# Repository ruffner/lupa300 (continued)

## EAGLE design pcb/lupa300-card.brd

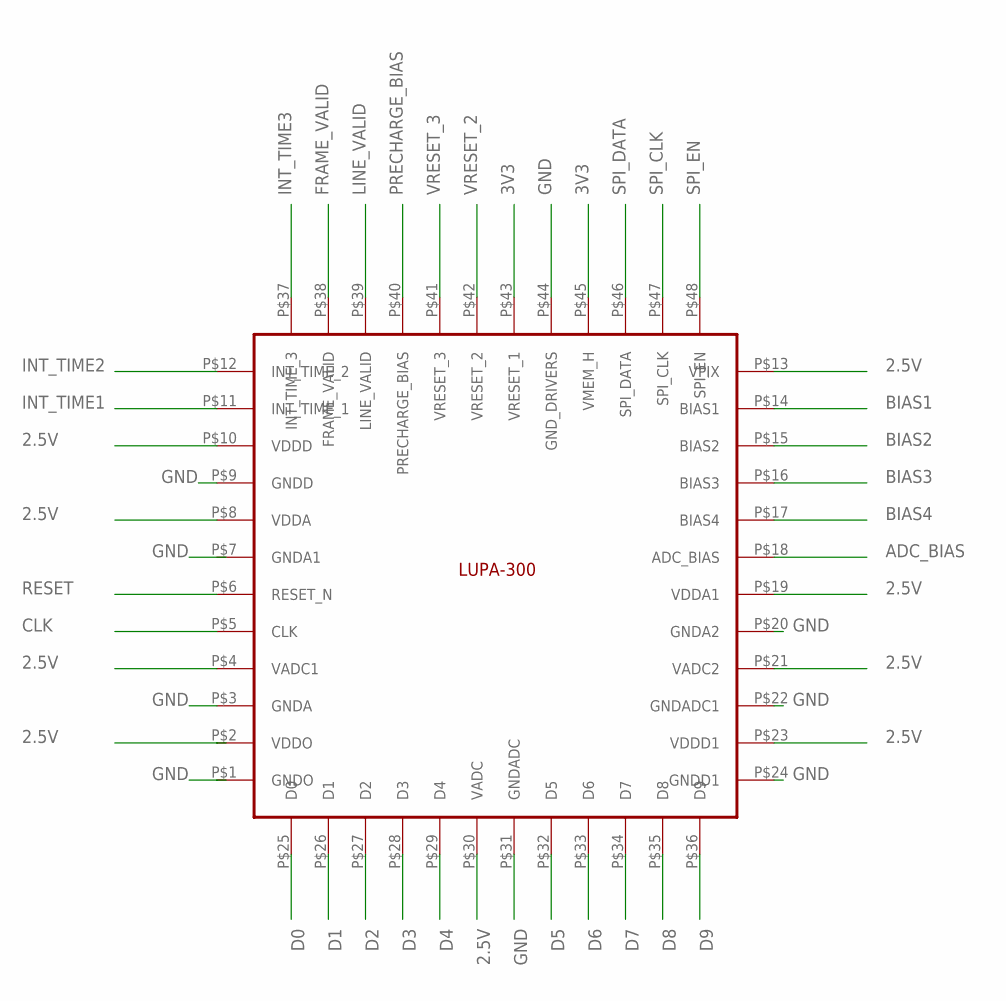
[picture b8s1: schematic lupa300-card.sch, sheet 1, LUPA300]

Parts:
U$1: LUPA300

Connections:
2.5V: U$1.P$2 (VDDO), U$1.P$4 (VADC1), U$1.P$8 (VDDA), U$1.P$10 (VDDD), U$1.P$13 (VPIX), U$1.P$19 (VDDA1), U$1.P$21 (VADC2), U$1.P$23 (VDDD1), U$1.P$30 (VADC); also elsewhere on the board
3V3: U$1.P$43 (VRESET_1), U$1.P$45 (VMEM_H); also elsewhere on the board
ADC_BIAS: U$1.P$18 (ADC_BIAS); also elsewhere on the board
BIAS1: U$1.P$14 (BIAS1); also elsewhere on the board
BIAS2: U$1.P$15 (BIAS2); also elsewhere on the board
BIAS3: U$1.P$16 (BIAS3); also elsewhere on the board
BIAS4: U$1.P$17 (BIAS4); also elsewhere on the board
CLK: U$1.P$5 (CLK); also elsewhere on the board
D0: U$1.P$25 (D0); also elsewhere on the board
D1: U$1.P$26 (D1); also elsewhere on the board
D2: U$1.P$27 (D2); also elsewhere on the board
D3: U$1.P$28 (D3); also elsewhere on the board
D4: U$1.P$29 (D4); also elsewhere on the board
D5: U$1.P$32 (D5); also elsewhere on the board
D6: U$1.P$33 (D6); also elsewhere on the board
D7: U$1.P$34 (D7); also elsewhere on the board
D8: U$1.P$35 (D8); also elsewhere on the board
D9: U$1.P$36 (D9); also elsewhere on the board
FRAME_VALID: U$1.P$38 (FRAME_VALID); also elsewhere on the board
GND: U$1.P$1 (GNDO), U$1.P$3 (GNDA), U$1.P$9 (GNDD), U$1.P$20 (GNDA2), U$1.P$22 (GNDADC1), U$1.P$24 (GNDD1), U$1.P$31 (GNDADC), U$1.P$44 (GND_DRIVERS); also elsewhere on the board
INT_TIME1: U$1.P$11 (INT_TIME_1); also elsewhere on the board
INT_TIME2: U$1.P$12 (INT_TIME_2); also elsewhere on the board
INT_TIME3: U$1.P$37 (INT_TIME_3); also elsewhere on the board
LINE_VALID: U$1.P$39 (LINE_VALID); also elsewhere on the board
PRECHARGE_BIAS: U$1.P$40 (PRECHARGE_BIAS); also elsewhere on the board
RESET: U$1.P$6 (RESET_N); also elsewhere on the board
SPI_CLK: U$1.P$47 (SPI_CLK); also elsewhere on the board
SPI_DATA: U$1.P$46 (SPI_DATA); also elsewhere on the board
SPI_EN: U$1.P$48 (SPI_EN); also elsewhere on the board
VRESET_2: U$1.P$42 (VRESET_2)
VRESET_3: U$1.P$41 (VRESET_3)

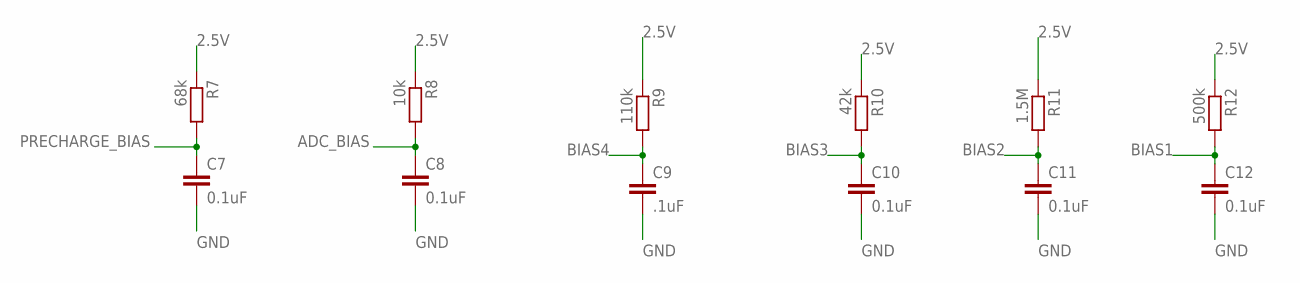
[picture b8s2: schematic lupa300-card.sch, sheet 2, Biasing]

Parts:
C7, C8, C10, C11, C12: 0.1uF; C0603K
C9: .1uF; C0603K
R7: 68k; R0603
R8: 10k; R0603
R9: 110k; R0603
R10: 42k; R0603
R11: 1.5M; R0603
R12: 500k; R0603

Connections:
2.5V: R7.1, R8.1, R9.1, R10.1, R11.1, R12.1; also elsewhere on the board
ADC_BIAS: C8.1, R8.2; also elsewhere on the board
BIAS1: C12.1, R12.2; also elsewhere on the board
BIAS2: C11.1, R11.2; also elsewhere on the board
BIAS3: C10.1, R10.2; also elsewhere on the board
BIAS4: C9.1, R9.2; also elsewhere on the board
GND: C7.2, C8.2, C9.2, C10.2, C11.2, C12.2; also elsewhere on the board
PRECHARGE_BIAS: C7.1, R7.2; also elsewhere on the board

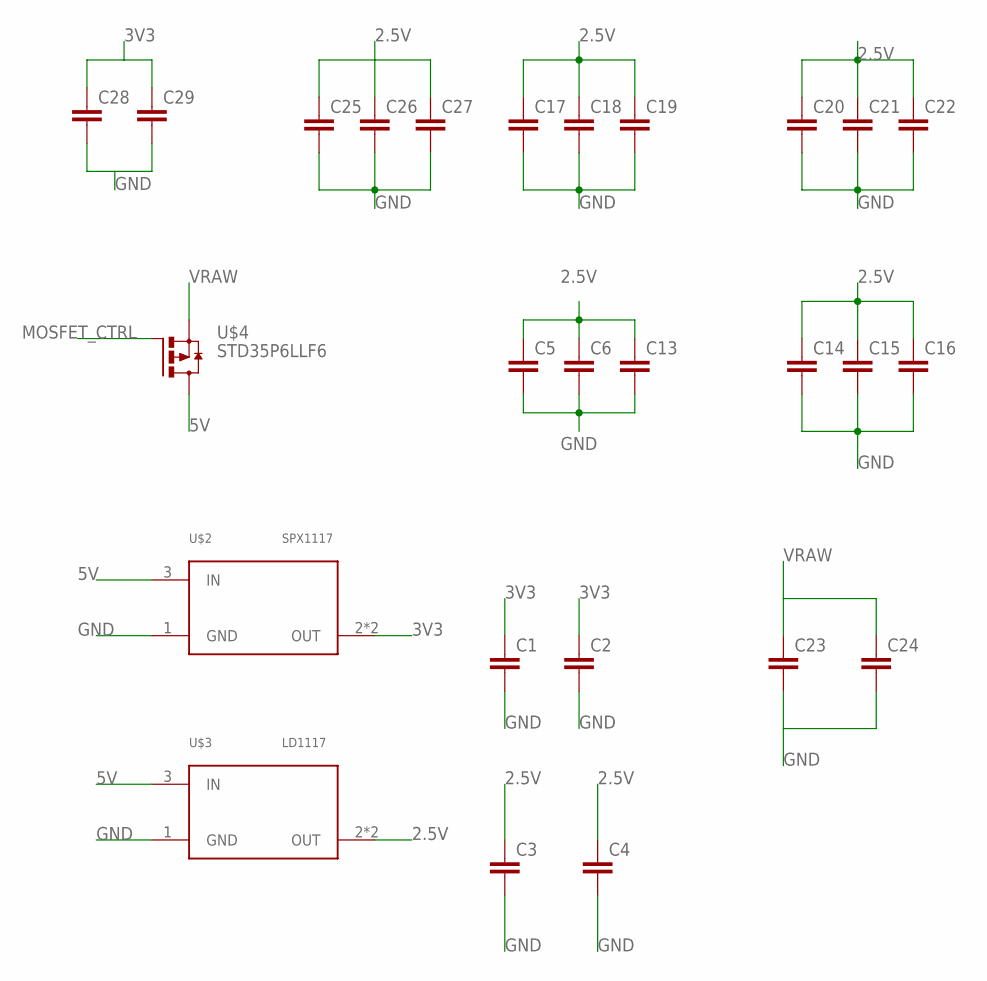
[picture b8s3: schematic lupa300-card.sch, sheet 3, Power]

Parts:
C1, C2, C3, C4: C-EUC1206K; C1206K
C5, C6, C13, C14, C15, C16, C17, C18, C19, C20, C21, C22, C25, C26, C27, C28, C29: C-EUC0603; C0603
C23, C24: C-EUC1206; C1206
U$2: SPX1117; SOT223
U$3: LD1117; SOT223
U$4: STD35P6LLF6; DPACK

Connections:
2.5V: C3.1, C4.1, C5.1, C6.1, C13.1, C14.1, C15.1, C16.1, C17.1, C18.1, C19.1, C20.1, C21.1, C22.1, C25.1, C26.1, C27.1, U$3.2 (OUT), U$3.4 (OUT); also elsewhere on the board
3V3: C1.1, C2.1, C28.1, C29.1, U$2.2 (OUT), U$2.4 (OUT); also elsewhere on the board
5V: U$2.3 (IN), U$3.3 (IN), U$4.2 (D)
GND: C1.2, C2.2, C3.2, C4.2, C5.2, C6.2, C13.2, C14.2, C15.2, C16.2, C17.2, C18.2, C19.2, C20.2, C21.2, C22.2, C23.2, C24.2, C25.2, C26.2, C27.2, C28.2, C29.2, U$2.1 (GND), U$3.1 (GND); also elsewhere on the board
MOSFET_CTRL: U$4.1 (G); also elsewhere on the board
VRAW: C23.1, C24.1, U$4.3 (S); also elsewhere on the board

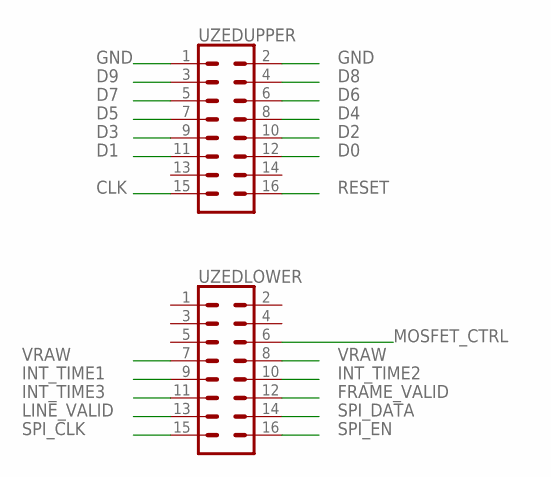
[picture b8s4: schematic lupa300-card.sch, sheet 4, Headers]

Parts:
UZEDLOWER: CONN_08X2; 2X8
UZEDUPPER: CONN_08X2; 2X8

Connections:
CLK: UZEDUPPER.15; also elsewhere on the board
D0: UZEDUPPER.12; also elsewhere on the board
D1: UZEDUPPER.11; also elsewhere on the board
D2: UZEDUPPER.10; also elsewhere on the board
D3: UZEDUPPER.9; also elsewhere on the board
D4: UZEDUPPER.8; also elsewhere on the board
D5: UZEDUPPER.7; also elsewhere on the board
D6: UZEDUPPER.6; also elsewhere on the board
D7: UZEDUPPER.5; also elsewhere on the board
D8: UZEDUPPER.4; also elsewhere on the board
D9: UZEDUPPER.3; also elsewhere on the board
FRAME_VALID: UZEDLOWER.12; also elsewhere on the board
GND: UZEDUPPER.1, UZEDUPPER.2; also elsewhere on the board
INT_TIME1: UZEDLOWER.9; also elsewhere on the board
INT_TIME2: UZEDLOWER.10; also elsewhere on the board
INT_TIME3: UZEDLOWER.11; also elsewhere on the board
LINE_VALID: UZEDLOWER.13; also elsewhere on the board
MOSFET_CTRL: UZEDLOWER.6; also elsewhere on the board
RESET: UZEDUPPER.16; also elsewhere on the board
SPI_CLK: UZEDLOWER.15; also elsewhere on the board
SPI_DATA: UZEDLOWER.14; also elsewhere on the board
SPI_EN: UZEDLOWER.16; also elsewhere on the board
VRAW: UZEDLOWER.7, UZEDLOWER.8; also elsewhere on the board

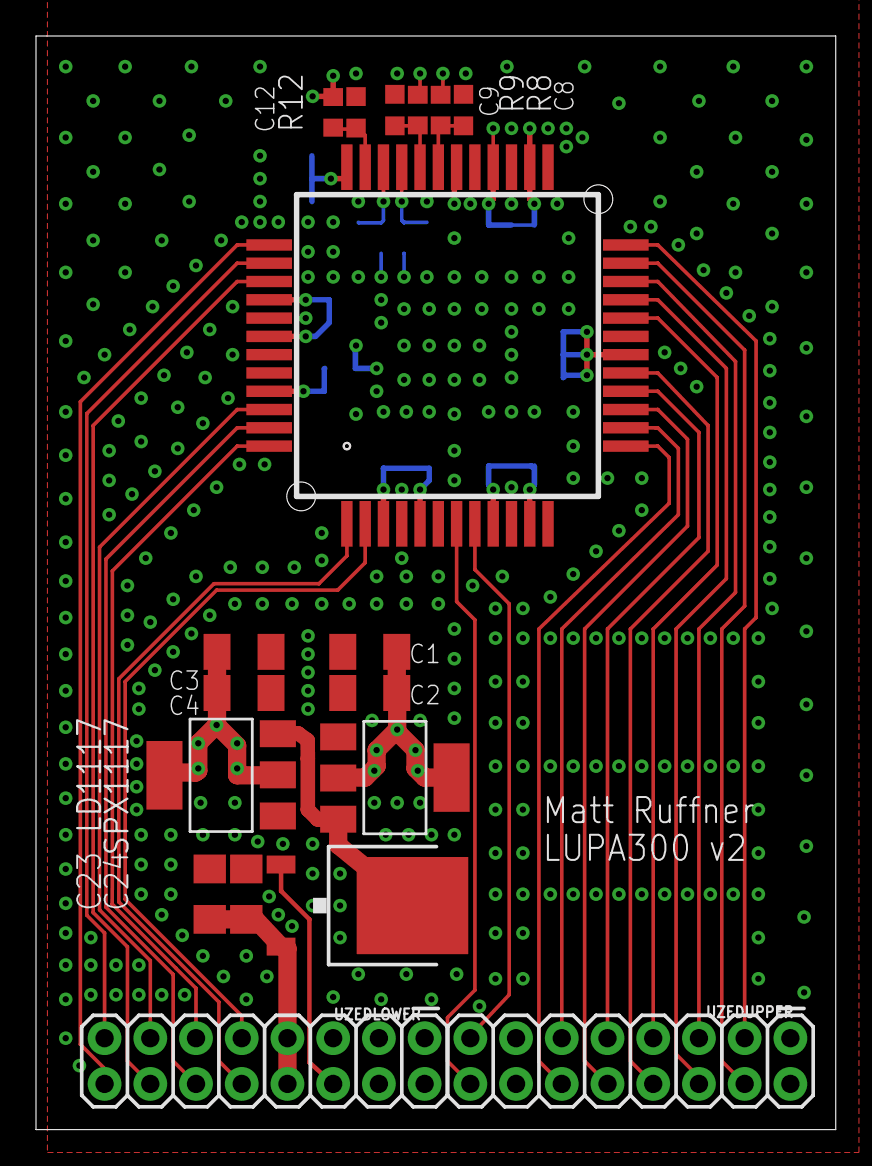
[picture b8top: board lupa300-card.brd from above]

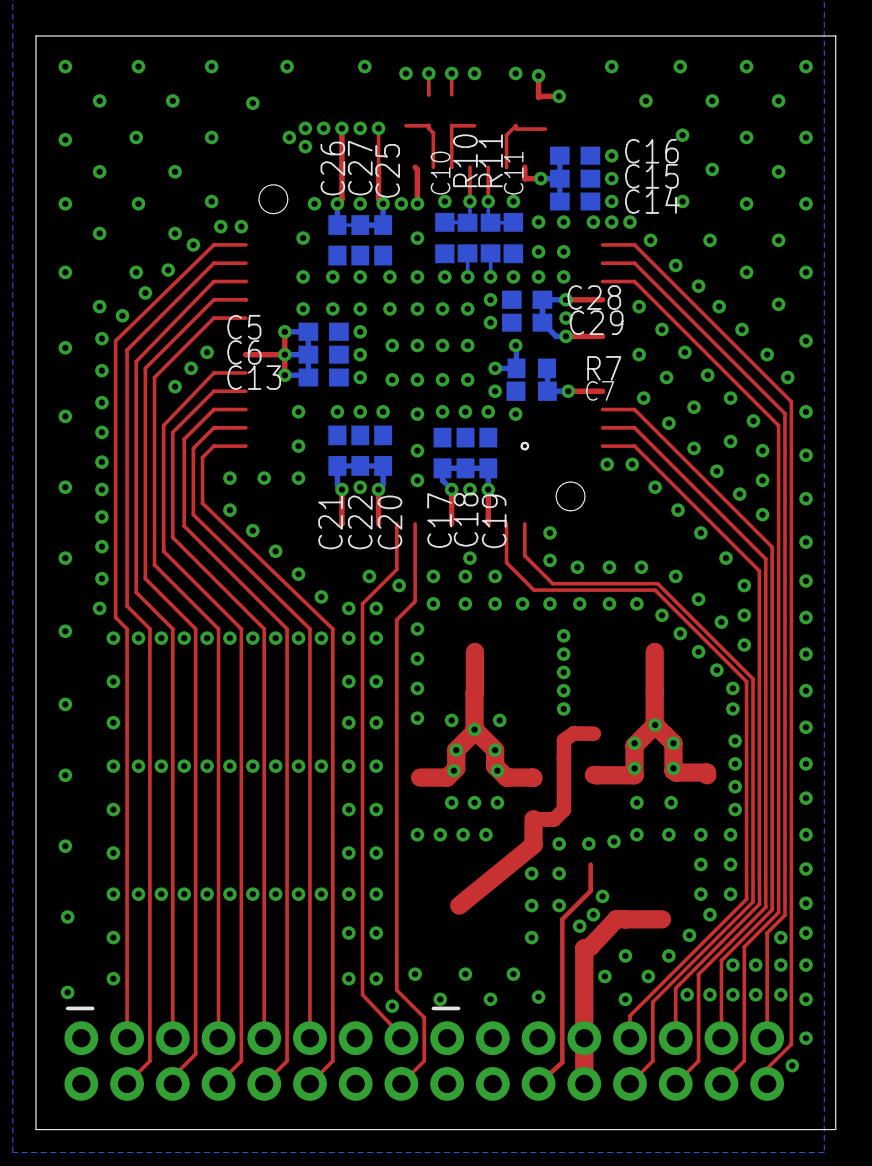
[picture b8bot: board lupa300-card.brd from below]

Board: 4 copper layers, 44.4 x 60.8 mm, 41 parts (23 on the bottom side), 32 nets.

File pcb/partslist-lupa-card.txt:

Partlist

Exported from lupa300-card.sch at 2/19/2018 2:41 PM

EAGLE Version 8.6.1 Copyright (c) 1988-2018 Autodesk, Inc.

Assembly variant: 

Part      Value          Device      Package  Library             Sheet

C1        100uF          C-EUC1206K  C1206K   rcl                 3
C2        10uF           C-EUC1206K  C1206K   rcl                 3
C3        100uF          C-EUC1206K  C1206K   rcl                 3
C4        10uF           C-EUC1206K  C1206K   rcl                 3
C5        1nF            C-EUC0603   C0603    rcl                 3
C6        10nF           C-EUC0603   C0603    rcl                 3
C7        0.1uF          C-EUC0603K  C0603K   rcl                 2
C8        0.1uF          C-EUC0603K  C0603K   rcl                 2
C9        .1uF           C-EUC0603K  C0603K   rcl                 2
C10       0.1uF          C-EUC0603K  C0603K   rcl                 2
C11       0.1uF          C-EUC0603K  C0603K   rcl                 2
C12       0.1uF          C-EUC0603K  C0603K   rcl                 2
C13       100nF          C-EUC0603   C0603    rcl                 3
C14       1nF            C-EUC0603   C0603    rcl                 3
C15       10nF           C-EUC0603   C0603    rcl                 3
C16       100nF          C-EUC0603   C0603    rcl                 3
C17       1nF            C-EUC0603   C0603    rcl                 3
C18       10nF           C-EUC0603   C0603    rcl                 3
C19       100nF          C-EUC0603   C0603    rcl                 3
C20       1nF            C-EUC0603   C0603    rcl                 3
C21       10nF           C-EUC0603   C0603    rcl                 3
C22       100nF          C-EUC0603   C0603    rcl                 3
C23       100uF          C-EUC1206   C1206    rcl                 3
C24       10uF           C-EUC1206   C1206    rcl                 3
C25       1nF            C-EUC0603   C0603    rcl                 3
C26       10nF           C-EUC0603   C0603    rcl                 3
C27       100nF          C-EUC0603   C0603    rcl                 3
C28       100uF          C-EUC0603   C0603    rcl                 3
C29       10uF           C-EUC0603   C0603    rcl                 3
R7        68k            R-EU_R0603  R0603    rcl                 2
R8        10k            R-EU_R0603  R0603    rcl                 2
R9        110k           R-EU_R0603  R0603    rcl                 2
R10       42k            R-EU_R0603  R0603    rcl                 2
R11       1.5M           R-EU_R0603  R0603    rcl                 2
R12       500k           R-EU_R0603  R0603    rcl                 2
U$1                      LUPA300     LUPA300  andon               1
U$2       SPX1117        SPX1117     SOT223   lupa300-components  3
U$3       LD1117         LD1117      SOT223   lupa300-components  3
U$4       STD35P6LLF6    STD35P6LLF6 DPACK    lupa300-components  3
UZEDLOWER                CONN_08X2   2X8      SparkFun-Connectors 4
UZEDUPPER                CONN_08X2   2X8      SparkFun-Connectors 4
